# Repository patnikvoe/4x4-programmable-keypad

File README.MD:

# 4x4 Programmable Keyboard
This project allows you to make a 4x4 programmable keypad. Its similar to standalone numpads, however you can programm each key individually to press one key, key combinations or even complex macros.

## Materials needed:
* 6 mm x 6 mm Tacticle Button (16x)
* 51k Resistor 0603 (16x)
* USB Micro Cable (1x)
* Sparkfun Pro Micro (5V or 3.3V shouldn't really matter) (1x)
* PCB milled with eagle files provided or perfboard + wiring cables
* 3D Printed Enclosure for looks (1x)
* screws depending on your enclosure design 

## Files
All files are stored in there respective folder. Code contains the C++ code for the Sparkfun Pro Micro. Eagle contains the Schematic and Board Files for the ECAD software "Autodesk Eagle".
### Code
The code was written and uploaded using the [hackable texteditor Atom](https://atom.io/) and the extentions [PlatformIO](https://platformio.org/platformio-ide), which are both available for Windows, Linux and macOS.

If you want to use the Arduino IDE, you need to perform two little changes.
Delete the following line or comment it out in the file `code/src/4x4-programmable-keypad.cpp` (Line 7).
```cpp
#include <Arduino.h>
```
Change the File name to `code/src/4x4-programmable-keypad.ino`.

### Quick start in programming your keys
Check the [Arduino Reference](https://www.arduino.cc/reference/en/language/functions/usb/keyboard/) for more detailed information.
#### Keyboard.press(), Keyboard.release(), Keyboard.releaseAll()
Press and release a single keys
```cpp
Keyboard.press(ALT);    // press the left ALT key
delay(50);              // Delays for 50 ms, you might be able to go lower, but 50 is a good starting point
Keyboard.release(ALT);  // Releases the left ALT key again; Alternatively Keyboard.releaseAll()
delay(200);             // Delay for 200 ms so it doesn't get run twice
```
Press and release a key combination
```cpp
Keyboard.press(STRG);   // press the left CTRL/STRG key
Keyboard.press('c');    // press the "c" key
delay(50);
Keyboard.releaseAll();  // release all keys
delay(200);
```
Press and release in a loop to repeat a set number of times
```cpp
for (int i=0;i<10;++i){   // repeat the key combination 10 times
  Keyboard.press(STRG);   // press the left CTRL/STRG key
  Keyboard.press('w');    // press 'w'
  delay(50);              // Delays for 50 ms, you might be able to go lower, but 50 is a good starting point
  Keyboard.release(ALT);  // Releases the left ALT key again; Alternatively Keyboard.releaseAll()
  delay(200);             // Delay for 200 ms so it doesn't get run twice
}
```
#### Keyboard.print(), Keyboard.println()
You can also send strings to your computer. For this you can use the following commands.
```cpp
Keyboard.print('My 4x4 Programmable Keypad ');
delay(50);
Keyboard.print('is awesome.');
delay(200);                     // Delay for 200 ms so it doesn't get run twice
```
Returns:
```
My 4x4 Programmable Keypad is awesome.
```
If you want to have a line break at the end of the line you can use println.
```cpp
Keyboard.println('My 4x4 Programmable Keypad ');
delay(50);
Keyboard.println('is awesome.');
delay(200);                     // Delay for 200 ms so it doesn't get run twice
```
Returns:
```
My 4x4 Programmable Keypad
is awesome.
```

### Eagle Files
Eagle Files were created in Version `9.0.1` of Autodesk Eagle. Newer versions should open it without problems, older versions might run into problems.

The folder `eagle/gerber-makerspace` contains the CAM files for the [UnternehmerTUM MakerSpace in Garching](https://www.maker-space.de). In case you have your own PCB mill or want to order some, you need to generate your own gerber files.

You might be able to get rid of the resistors, if you change all `pinMode` from `INPUT` to `INPUT_PULLUP` in the file `code/src/4x4-programmable-keypad.cpp`. **I have  not tested this, so try this at your own risk.**
```cpp
pinMode(key[0][0], INPUT);
```
to
```cpp
pinMode(key[0][0], INPUT_PULLUP);
```
You might also need to change the if-Statements from checking `HIGH` to `LOW`:
```cpp
if (digitalRead(key[0][0]) == HIGH)
```
to
```cpp
if (digitalRead(key[0][0]) == LOW)
```

### Enclosure
`Work in progress`

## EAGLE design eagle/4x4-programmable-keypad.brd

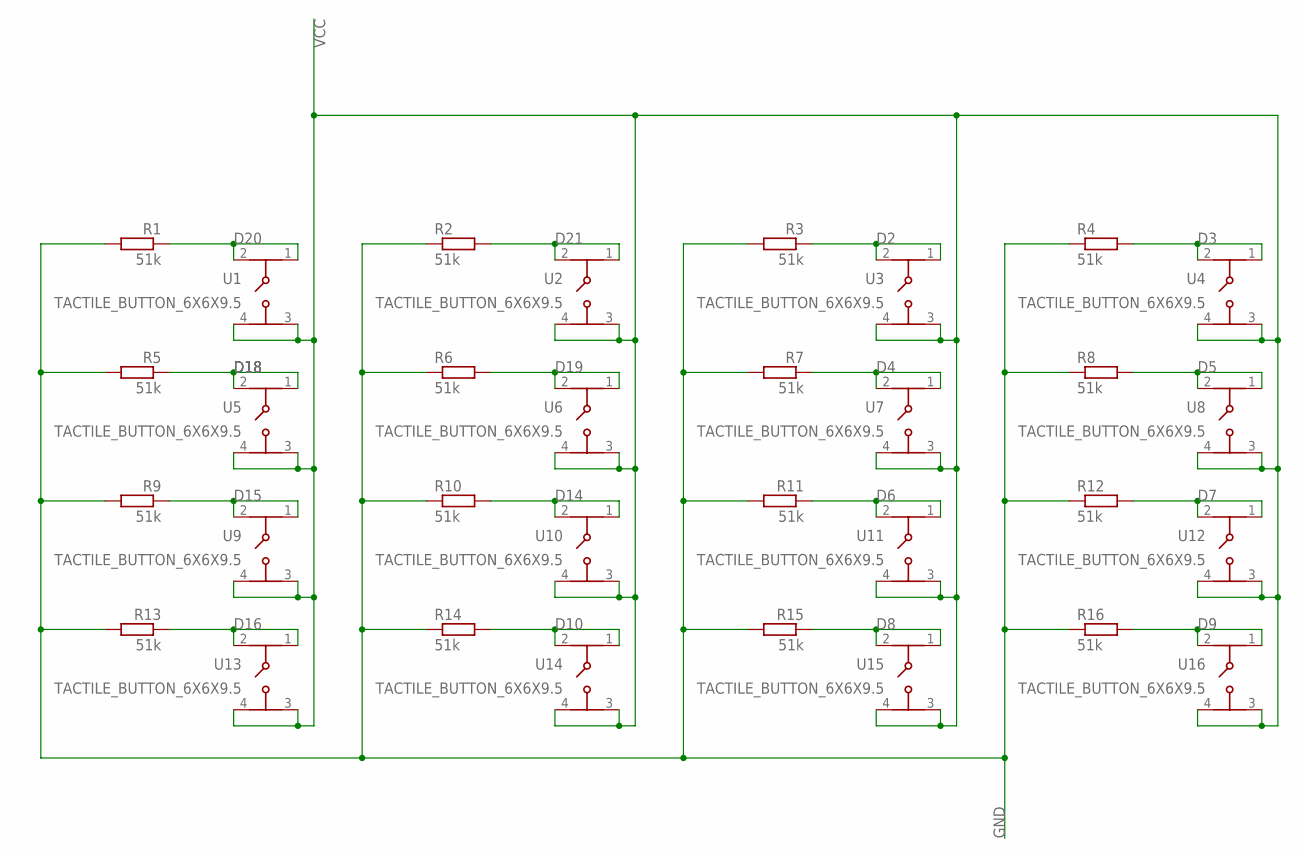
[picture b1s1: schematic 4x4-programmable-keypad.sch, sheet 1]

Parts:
R1, R2, R3, R4, R5, R6, R7, R8, R9, R10, R11, R12, R13, R14, R15, R16: 51k; R0603
U1, U2, U3, U4, U5, U6, U7, U8, U9, U10, U11, U12, U13, U14, U15, U16: TACTILE_BUTTON_6X6X9.5; TACTILE_SWITCH_PTH_6.0MM

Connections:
D2: R3.1, U3.1, U3.2 (3); also elsewhere on the board
D3: R4.2, U4.1, U4.2 (3); also elsewhere on the board
D4: R7.1, U7.1, U7.2 (3); also elsewhere on the board
D5: R8.2, U8.1, U8.2 (3); also elsewhere on the board
D6: R11.1, U11.1, U11.2 (3); also elsewhere on the board
D7: R12.2, U12.1, U12.2 (3); also elsewhere on the board
D8: R15.1, U15.1, U15.2 (3); also elsewhere on the board
D9: R16.2, U16.1, U16.2 (3); also elsewhere on the board
D10: R14.2, U14.1, U14.2 (3); also elsewhere on the board
D14: R10.2, U10.1, U10.2 (3); also elsewhere on the board
D15: R9.1, U9.1, U9.2 (3); also elsewhere on the board
D16: R13.1, U13.1, U13.2 (3); also elsewhere on the board
D18: R5.1, U5.1, U5.2 (3); also elsewhere on the board
D19: R6.2, U6.1, U6.2 (3); also elsewhere on the board
D20: R1.1, U1.1, U1.2 (3); also elsewhere on the board
D21: R2.2, U2.1, U2.2 (3); also elsewhere on the board
GND: R1.2, R2.1, R3.2, R4.1, R5.2, R6.1, R7.2, R8.1, R9.2, R10.1, R11.2, R12.1, R13.2, R14.1, R15.2, R16.1; also elsewhere on the board
VCC: U1.3 (2), U1.4, U2.3 (2), U2.4, U3.3 (2), U3.4, U4.3 (2), U4.4, U5.3 (2), U5.4, U6.3 (2), U6.4, U7.3 (2), U7.4, U8.3 (2), U8.4, U9.3 (2), U9.4, U10.3 (2), U10.4, U11.3 (2), U11.4, U12.3 (2), U12.4, U13.3 (2), U13.4, U14.3 (2), U14.4, U15.3 (2), U15.4, U16.3 (2), U16.4; also elsewhere on the board

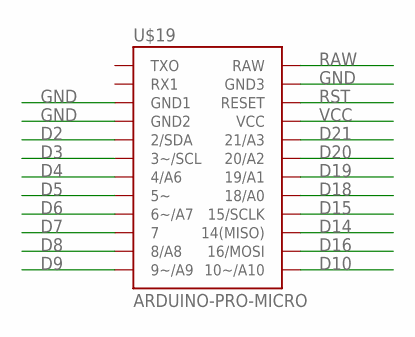
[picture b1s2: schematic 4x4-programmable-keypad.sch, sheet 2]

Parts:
U$19: ARDUINO-PRO-MICRO; SPARKFUN_PRO_MICRO

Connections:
D2: U$19.2/SDA; also elsewhere on the board
D3: U$19.3~/SCL; also elsewhere on the board
D4: U$19.4/A6; also elsewhere on the board
D5: U$19.5~; also elsewhere on the board
D6: U$19.6~/A7; also elsewhere on the board
D7: U$19.7; also elsewhere on the board
D8: U$19.8/A8; also elsewhere on the board
D9: U$19.9~/A9; also elsewhere on the board
D10: U$19.10~/A10; also elsewhere on the board
D14: U$19.14/MISO (14(MISO)); also elsewhere on the board
D15: U$19.15/SCLK; also elsewhere on the board
D16: U$19.16/MOSI; also elsewhere on the board
D18: U$19.18/A0; also elsewhere on the board
D19: U$19.19/A1; also elsewhere on the board
D20: U$19.20/A2; also elsewhere on the board
D21: U$19.21/A3; also elsewhere on the board
GND: U$19.GND1, U$19.GND2, U$19.GND3; also elsewhere on the board
RAW: U$19.RAW
RST: U$19.RST (RESET)
VCC: U$19.VCC; also elsewhere on the board

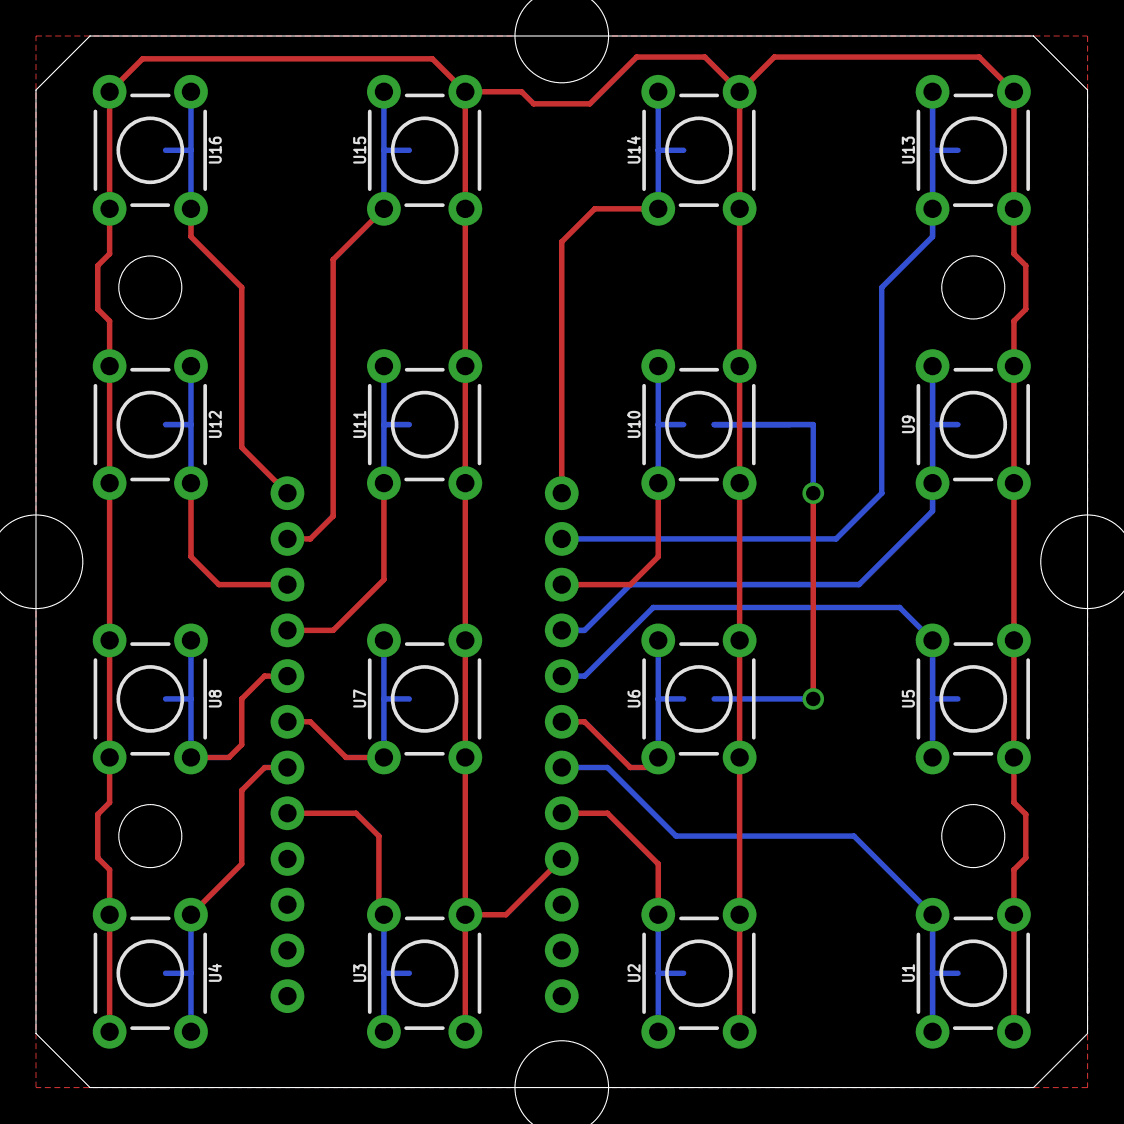
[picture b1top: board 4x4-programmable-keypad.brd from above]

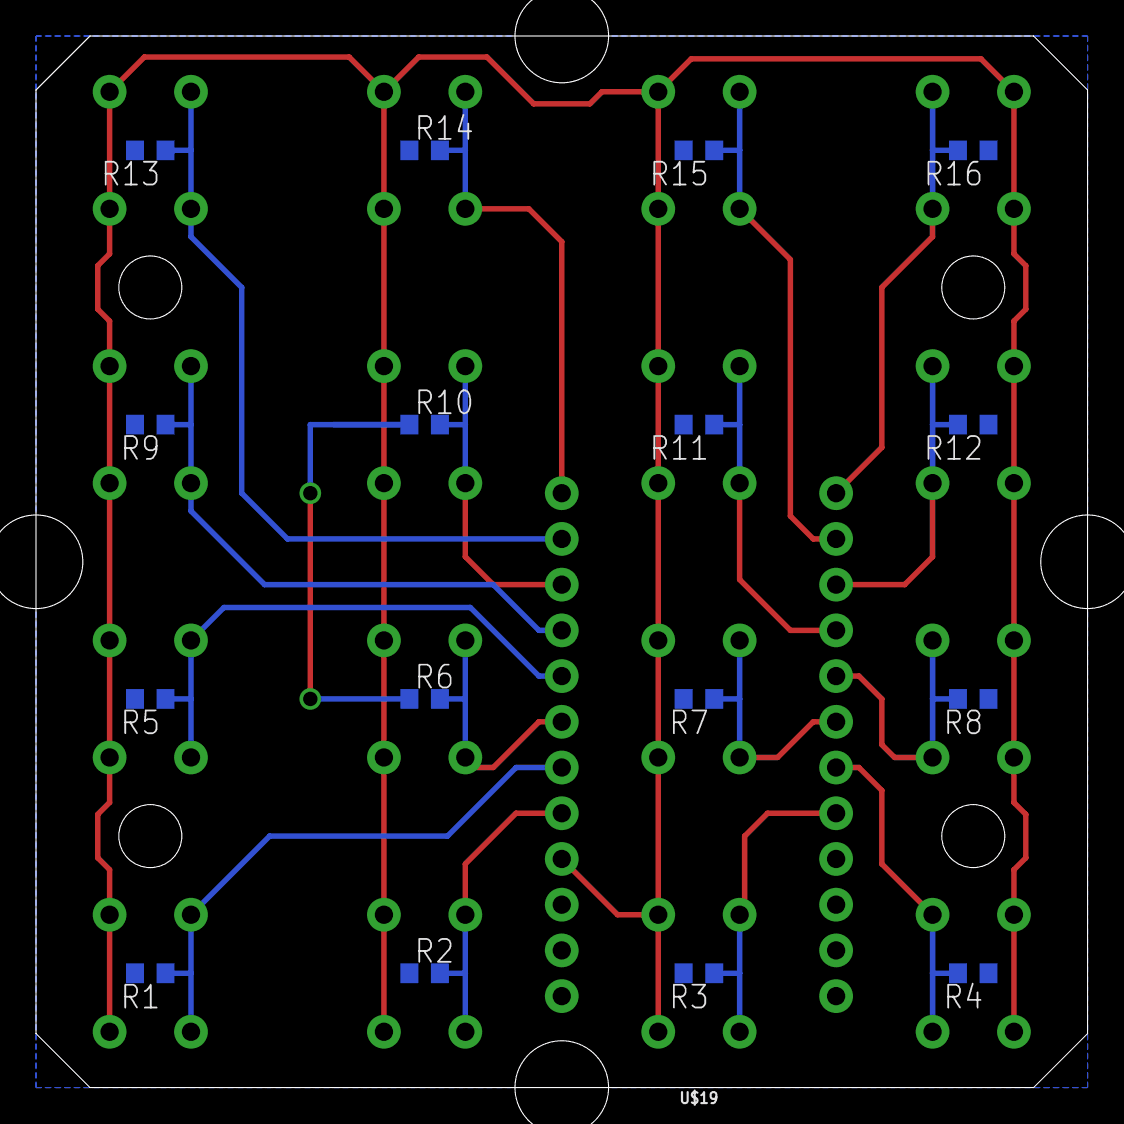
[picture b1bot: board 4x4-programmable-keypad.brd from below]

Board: 2 copper layers, 58.4 x 58.4 mm, 33 parts (17 on the bottom side), 18 nets.

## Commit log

2018-05-25 Eagle files update
2018-05-25 Gerber Files for maker-space.de
2018-05-25 Arduino Code 0.1
2018-05-25 gitignore added
2018-05-25 folder for eagle files created, eagle files moved
2018-05-29 Update board and schematic
2018-05-29 New CAM Export
2018-05-29 renamed cpp file, code adjusted
2018-05-29 Hardware keys adjusted
2018-06-05 updated 4x4-programmable-keypad
2018-06-05 generated Readme file
2018-06-05 Test
2018-06-05 formated Readme
2018-06-05 Gerber updated
2018-06-05 added new headlines to Readme
2018-06-06 renamed code folder
2018-06-06 not neccessary
2018-06-06 updated Readme file
2018-06-06 Readme file
2018-06-06 Code updated
2018-06-06 Formating in code
2018-06-06 updated Eagle readme
2018-06-06 updated readme Eagle
2018-06-06 Readme expanded
2018-06-06 Keyboard.println info text
2018-06-06 boardlayout inserted picture
2018-06-06 Readme updated
